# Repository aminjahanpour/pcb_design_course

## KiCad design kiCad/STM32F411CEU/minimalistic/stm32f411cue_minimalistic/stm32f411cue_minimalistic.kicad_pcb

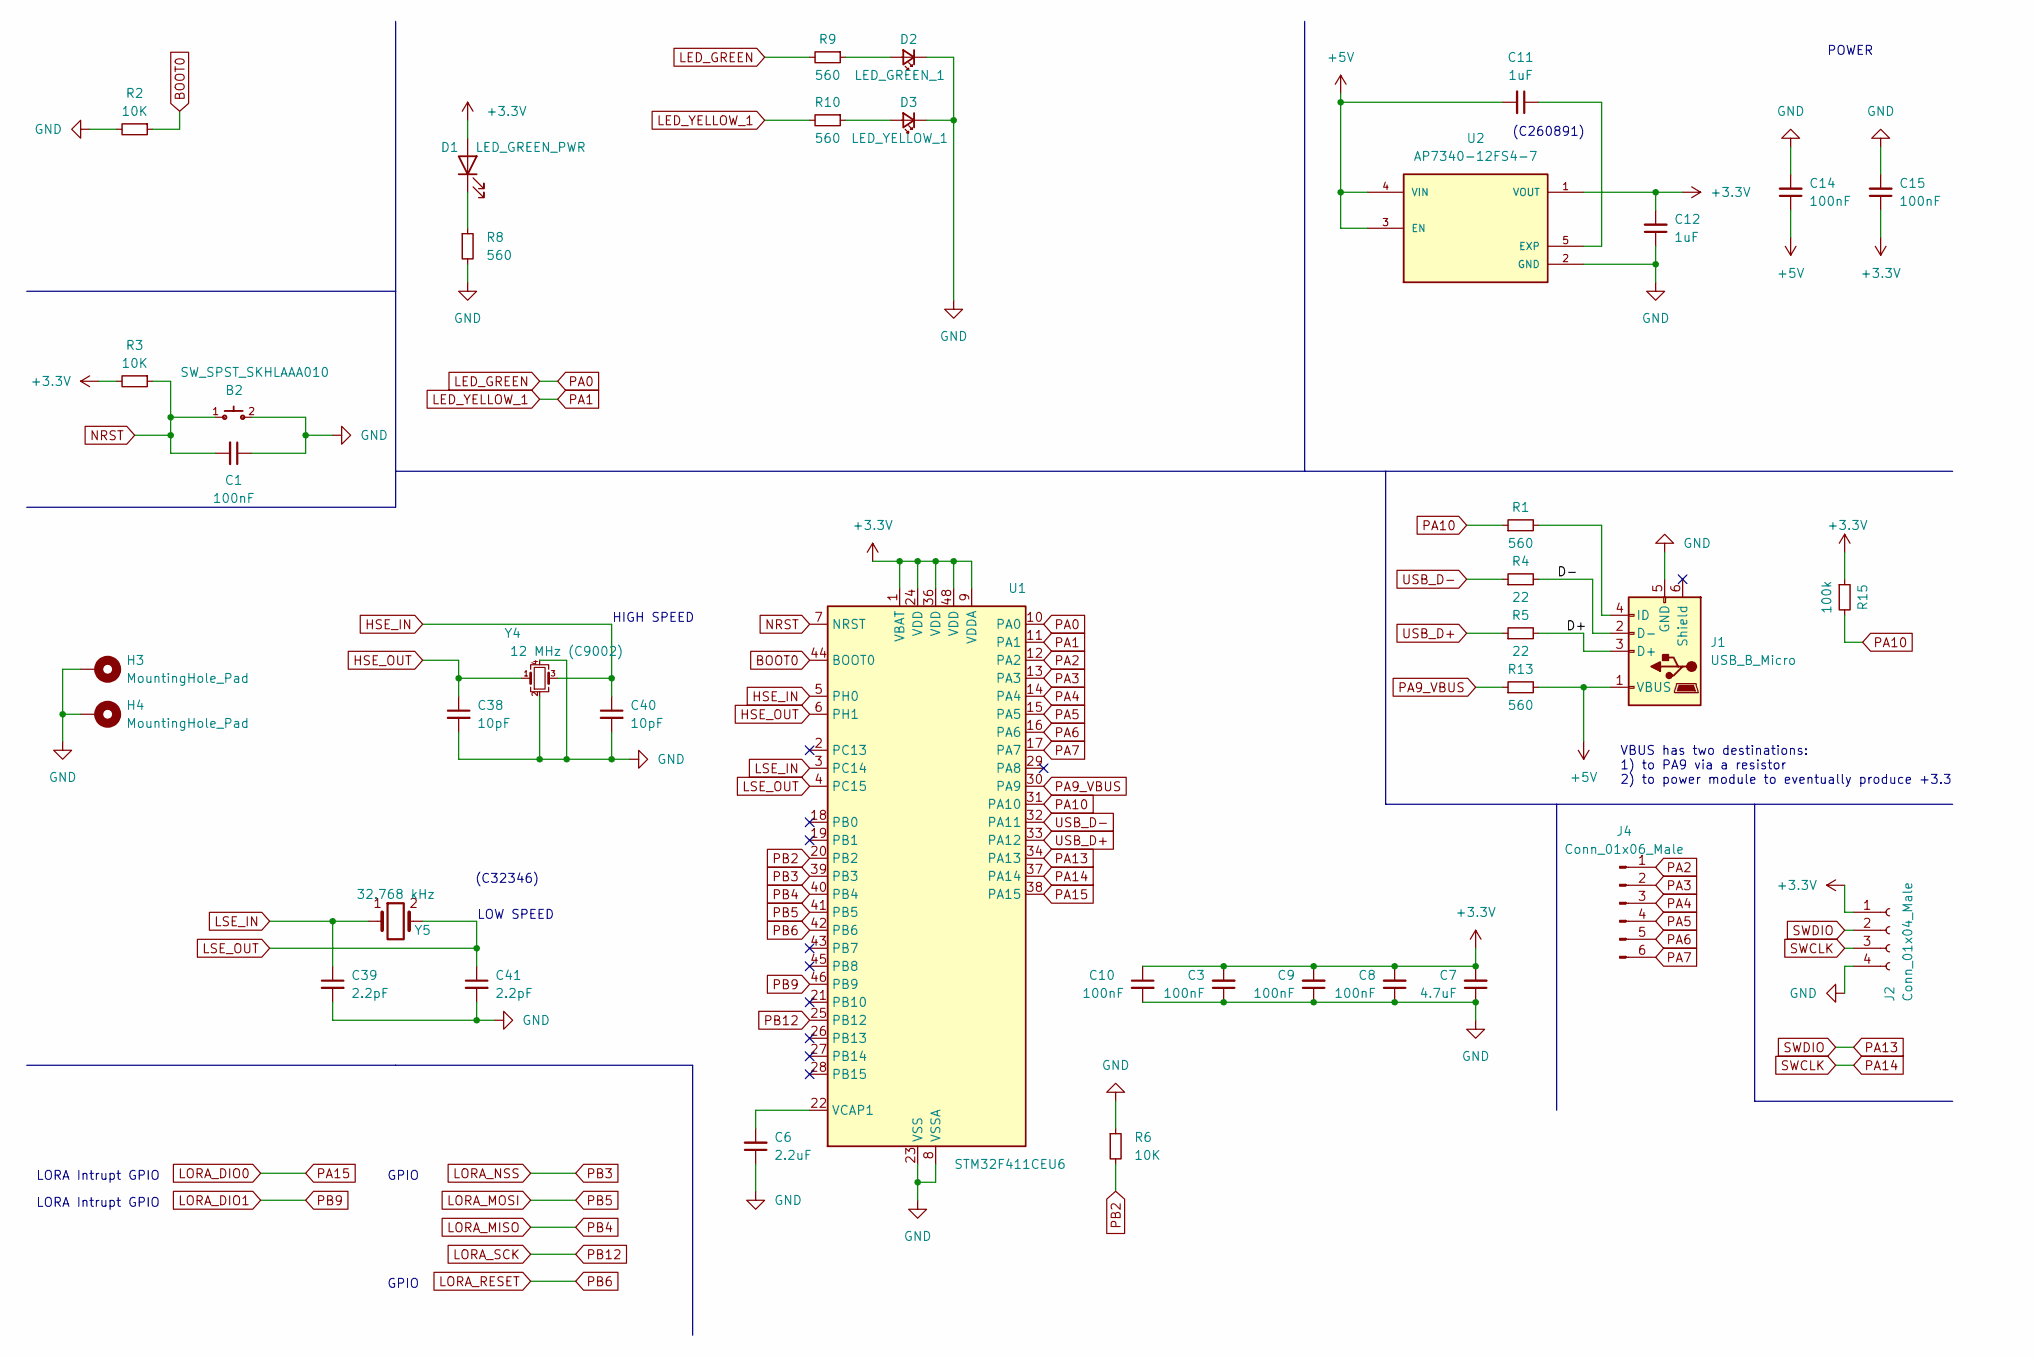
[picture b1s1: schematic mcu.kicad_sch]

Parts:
B2: SW_SPST_SKHLAAA010; SKHLAAA010; LCSC Part # C470263
C1, C3, C8, C9, C10: 100nF; C_0402_1005Metric; LCSC Part # C1525
C6: 2.2uF; C_0402_1005Metric; LCSC Part # C12530
C7: 4.7uF; C_0402_1005Metric; LCSC Part # C23733
C11, C12: 1uF; C_0603_1608Metric; LCSC Part # C15849
C14, C15: 100nF; C_0603_1608Metric; LCSC Part # C14663
C38, C40: 10pF; C_0402_1005Metric; LCSC Part # C32949
C39, C41: 2.2pF; C_0402_1005Metric; LCSC Part # C1559
D1: LED_GREEN_PWR; LED_0603_1608Metric; LCSC Part # C84264
D2: LED_GREEN_1; LED_0603_1608Metric; LCSC Part # C84264
D3: LED_YELLOW_1; LED_0603_1608Metric; LCSC Part # C72038
H3, H4: MountingHole_Pad; MountingHole_2.2mm_M2_Pad
J1: USB_B_Micro; USB_Micro-B_Molex-105017-0001; LCSC Part # C2842944
J2: Conn_01x04_Male; PinHeader_1x04_P2.54mm_Vertical; LCSC Part # C2938401
J4: Conn_01x06_Male; PinHeader_1x06_P2.54mm_Vertical
R1, R8, R9, R10, R13: 560; R_0603_1608Metric; LCSC Part # C163936
R2, R3, R6: 10K; R_0402_1005Metric; LCSC Part # C174175
R4, R5: 22; R_0402_1005Metric; LCSC Part # C25092
R15: 100k; R_0402_1005Metric; LCSC Part # C25741
U1: STM32F411CEU6; QFN-48-1EP_7x7mm_P0.5mm_EP5.6x5.6mm; LCSC Part # C60420
U2: AP7340-12FS4-7; VREG_AP7340D-25FS4-7; LCSC Part # C260891
Y4: 12 MHz (C9002); Crystal_SMD_3225-4Pin_3.2x2.5mm; LCSC Part # C9002
Y5: 32.768 kHz; Crystal_SMD_3215-2Pin_3.2x1.5mm; LCSC Part # C32346

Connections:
+3.3V: C3.2, C7.2, C8.2, C9.2, C10.1, C12.2, C15.1, D1.2 (A), J2.1, R3.2, R15.1, U1.1 (VBAT), U1.9 (VDDA), U1.24 (VDD), U1.36 (VDD), U1.48 (VDD), U2.1 (VOUT)
+5V: C11.2, C14.1, J1.1 (VBUS), R13.2, U2.3 (EN), U2.4 (VIN)
/MCU/D+: J1.3 (D+), R5.2
/MCU/D-: J1.2 (D-), R4.2
BOOT0: R2.1, U1.44 (BOOT0)
GND: B2.2, C1.1, C3.1, C6.1, C7.1, C8.1, C9.1, C10.2, C12.1, C14.2, C15.2, C38.2, C39.2, C40.2, C41.2, D2.1 (K), D3.1 (K), H3.1 (1_1), H4.1 (1_1), J1.5 (GND), J2.4, R2.2, R6.1, R8.2, U1.8 (VSSA), U1.23 (VSS), U1.35 (VSS), U1.47 (VSS), U1.49 (VSS), U2.2 (GND), Y4.2, Y4.4
HSE_IN: C40.1, U1.5 (PH0), Y4.3
HSE_OUT: C38.1, U1.6 (PH1), Y4.1
LED_GREEN: R9.2, U1.10 (PA0)
LED_YELLOW_1: R10.2, U1.11 (PA1)
LORA_DIO0: U1.38 (PA15)
LORA_DIO1: U1.46 (PB9)
LORA_MISO: U1.40 (PB4)
LORA_MOSI: U1.41 (PB5)
LORA_NSS: U1.39 (PB3)
LORA_RESET: U1.42 (PB6)
LORA_SCK: U1.25 (PB12)
LSE_IN: C39.1, U1.3 (PC14), Y5.1
LSE_OUT: C41.1, U1.4 (PC15), Y5.2
NRST: B2.1, C1.2, R3.1, U1.7 (NRST)
unnamed: D1.1 (K), R8.1
unnamed: D2.2 (A), R9.1
unnamed: D3.2 (A), R10.1
unnamed: J1.4 (ID), R1.2
unnamed: C6.2, U1.22 (VCAP1)
unnamed: C11.1, U2.5 (EXP)
PA2: J4.1, U1.12 (PA2)
PA3: J4.2, U1.13 (PA3)
PA4: J4.3, U1.14 (PA4)
PA5: J4.4, U1.15 (PA5)
PA6: J4.5, U1.16 (PA6)
PA7: J4.6, U1.17 (PA7)
PA9_VBUS: R13.1, U1.30 (PA9)
PA10: R1.1, R15.2, U1.31 (PA10)
PA13: J2.2, U1.34 (PA13)
PA14: J2.3, U1.37 (PA14)
PB2: R6.2, U1.20 (PB2)
USB_D+: R5.1, U1.33 (PA12)
USB_D-: R4.1, U1.32 (PA11)

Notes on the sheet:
VBUS has two destinations: 1) to PA9 via a resistor 2) to power module to eventually produce +3.3
LORA Intrupt GPIO
(C32346)
POWER
LOW SPEED
GPIO
HIGH SPEED
(C260891)

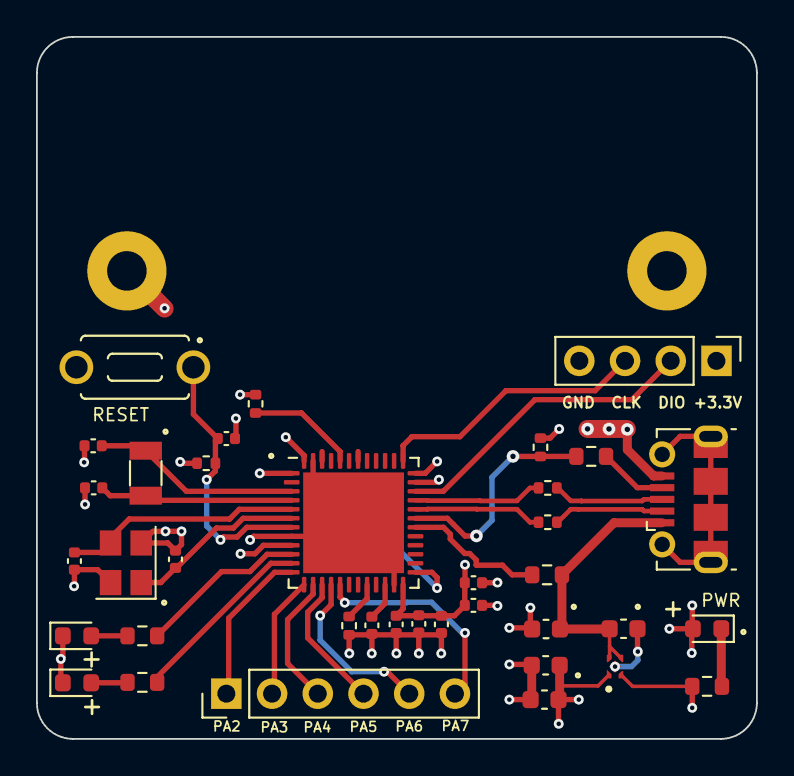
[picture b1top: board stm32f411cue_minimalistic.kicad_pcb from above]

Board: 4 copper layers, 40.0 x 39.0 mm, 39 parts (0 on the bottom side), 32 nets.
